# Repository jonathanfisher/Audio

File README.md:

# Overview
Now that I work for an audio company, I should really learn more about the various technology that goes into making things sound great. I've decided to spend some time designing my own audio setup (outside of making my own speaker). This project is intended as a learning exercise, not as a product to sell. As such, the commits here may take interesting twists and turns.

# Repository
This repository contains the design files for the PCBs I intend to make. The idea is to eventually design the following stages:

1. [USB](#USB)
2. [DAC](#DAC)
3. [Amplifier](#Amplifier)

I intend to design these as discrete boards that can be chained together. This modular design should allow me to more easily iterate in things I care about. I imagine that I will make mistakes along the way, and will have to re-spin boards.

## USB
This stage is intended to be the interface between a digital audio source (e.g. computer) and the rest of the audio system. USB seemed to be a reasonable medium to use for this.

## DAC
This stage is responsible for receiving a stream of digital signals and converting it to an analog output that can be converted to sound by a speaker.

## Amplifier
This stage is responsible for taking the output of the DAC and amplifying it so that the speaker(s) output the desired level of sound.

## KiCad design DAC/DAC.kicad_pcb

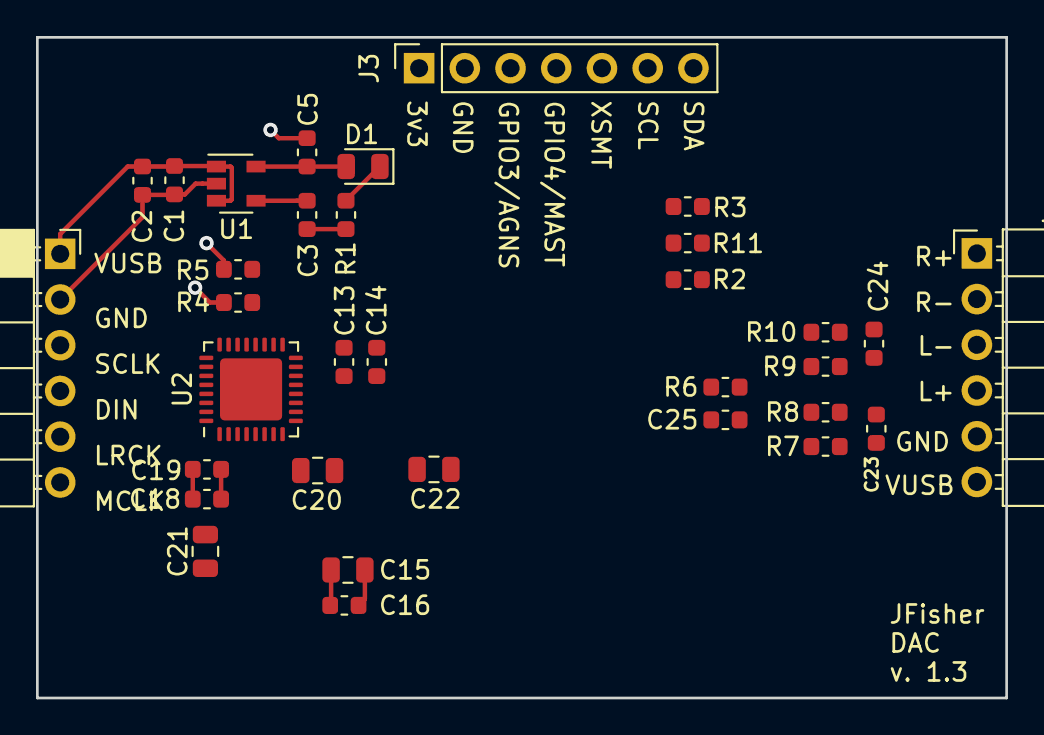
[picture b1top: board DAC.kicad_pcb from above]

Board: 4 copper layers, 53.8 x 36.7 mm, 33 parts (0 on the bottom side), 30 nets.

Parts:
C1, C13, C18: 10uF; C_0603_1608Metric
C2, C14, C16, C19: 0.1uF; C_0603_1608Metric
C3: 0.01uF; C_0603_1608Metric
C5: 1uF; C_0603_1608Metric
C15, C20, C22: 2.2uF; C_0805_2012Metric
C21: 0.1uF; C_0805_2012Metric
C23, C24: 1000pF; C_0603_1608Metric
C25: 1.0uF; C_0603_1608Metric
D1: LED_3v3; LED_0805_2012Metric
J1: Conn_01x06; PinSocket_1x06_P2.54mm_Horizontal
J2: Conn_01x06; PinHeader_1x06_P2.54mm_Horizontal
J3: Conn_01x07_Male; PinSocket_1x07_P2.54mm_Vertical
R1: 360; R_0603_1608Metric
R2, R11: 4.7k; R_0603_1608Metric
R3, R4, R5: 4.99k; R_0603_1608Metric
R6: 0; R_0603_1608Metric
R7, R8, R9, R10: 499; R_0603_1608Metric
U1: TPS73633DBV; SOT-23-5
U2: PCM5242RHB; Texas_S-PVQFN-N32_EP3.45x3.45mm

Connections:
+3V3: C5.1, C13.1, C14.1, C15.1, C16.1, C18.1, C19.1, D1.2, J3.1, R2.1, R3.2, R4.2, R11.1, U1.5, U2.4, U2.5, U2.14
DACL+: C23.1, J2.4, R7.1
DACL-: C23.2, J2.3, R8.1
DACR+: C24.2, J2.1, R10.1
DACR-: C24.1, J2.2, R9.1
GND: C1.2, C2.2, C3.2, C5.2, C13.2, C14.2, C15.2, C16.2, C18.2, C19.2, C21.2, C22.2, C25.2, J1.2, J2.5, J3.2, R1.2, R5.2, R6.1, U1.2, U2.3, U2.7, U2.15, U2.22, U2.32
GPIO3_AGNS: J3.3, U2.21
GPIO4_MAST: J3.4, U2.20
GPIO5_ATT0: J1.6, U2.19
GPIO6_FLT: U2.25, U2.26
I2S_DIN: J1.4, U2.28
I2S_LRCK: J1.5, U2.31
I2S_SCLK: J1.3, U2.27
MODE1: R5.1, U2.23
MODE2: R4.1, U2.24
unnamed: C3.1, U1.4
unnamed: C20.1, U2.6
unnamed: C20.2, U2.8
unnamed: C21.1, U2.2
unnamed: C22.1, U2.9
unnamed: C25.1, R6.2, U2.16
unnamed: D1.1, R1.1
OUTL_N: R8.2, U2.11
OUTL_P: R7.2, U2.10
OUTR_N: R9.2, U2.12
OUTR_P: R10.2, U2.13
SCL_MC_ATT1: J3.6, R2.2, U2.18
SDA_MOSI_ATT2: J3.7, R11.2, U2.17
VUSB: C1.1, C2.1, J1.1, J2.6, U1.1, U1.3
XSMT: J3.5, R3.1, U2.1

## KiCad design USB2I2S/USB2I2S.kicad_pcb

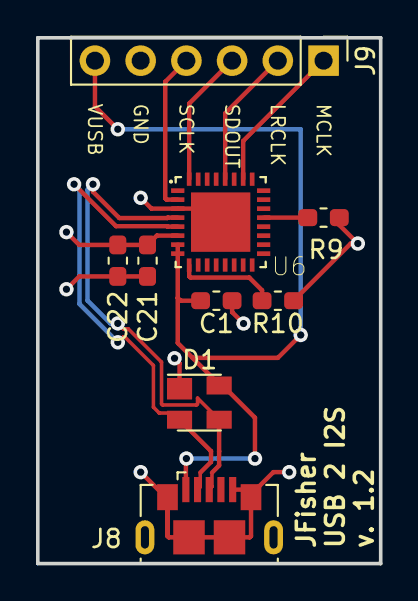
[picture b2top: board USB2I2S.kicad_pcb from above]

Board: 4 copper layers, 19.1 x 29.2 mm, 9 parts (0 on the bottom side), 11 nets.

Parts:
C1, C21: 1uF; C_0603_1608Metric_Pad1.05x0.95mm_HandSolder
C22: 0.1uF; C_0603_1608Metric_Pad1.05x0.95mm_HandSolder
D1: SP0503BAHT; SOT-143
J8: USB_B_Micro; USB_Micro-B_GCT_USB3076-30-A
J9: Conn_01x06_Male; PinHeader_1x06_P2.54mm_Vertical
R9, R10: 4.7K; R_0603_1608Metric_Pad1.05x0.95mm_HandSolder
U6: CP2615-A01-GM; QFN50P500X500X90-33N

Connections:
GND: C1.2, C21.2, C22.2, D1.1, J8.5, J8.6, J9.5, U6.3, U6.33
I2S_LRCLK: J9.2, U6.28
I2S_MCLK: J9.1, U6.26
I2S_SCLK: J9.4, U6.2
I2S_SDOUT: J9.3, U6.32
unnamed: R9.2, U6.21
unnamed: R10.2, U6.9
USB_DN: D1.2, J8.2, U6.5
USB_DP: D1.3, J8.3, U6.4
VBUS_IN: C1.1, D1.4, J8.1, J9.6, U6.7, U6.8
VCC: C21.1, C22.1, R9.1, R10.1, U6.6

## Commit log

2019-02-13 Initial commit with basic files for Audio DAC
2019-02-15 Add library containing CP2615 part
2019-02-15 Add schematic for the USB -> I2S stage
2019-02-15 Bring in project with multi-page design
2019-02-19 Add components for creating 3v3 for the DAC power rails
2019-03-07 Schematic and board file for USB2I2S dongle
2019-03-07 Update gitignore to account for more temp files
2019-03-11 Start designing the DAC stage
2019-03-17 Remove old and unused scratch files
2019-03-18 Create symbol for the PCM5242 DAC from TI
2019-03-18 Add sheet for the actual DAC part
2019-03-18 Add sheet for power conversion (USB -> 3v3 for now)
2019-03-18 Add Sheets for the I/O for this board. Still WIP on output
2019-03-18 Bring changes together in outmost sheet. This should just pull together the various subsheets
2019-03-18 Remove unused I/V stage on output of DAC
2019-03-19 Add new sheet for amplifier (post i-v stage)
    I'm not sure if I'll stick with this here; my thinking is that it makes
    sense to keep the post I-V stage amplifier on the same PCB as the DAC to
    minimize noise on the amplifier input. I imagine that PCB interconnects
    would cause a fairly significant amount of noise, so I'd like to avoid
    that.
2019-03-19 Remove absolute paths
2019-03-21 Adding support for headphone amp (WIP)
2019-03-22 Started layout of the DAC board
2019-03-25 Update USB2I2S board to fix routing issue
    - Fixed issue where VCC was connected to VUSB
    - Converted PCB to 4-layer board with Vcc and GND planes
    - Removed headers for pins that I'm not expecting to use
    - Re-layed out the PCB.
2019-03-25 Update KiCad and minor adjustments (cosmetic)
    Rotated the decoupling caps on Vcc to ensure that the blind vias were
    away from the differential USB signal traces.
2019-03-26 Remove extraneous directory (DAC/DAC/ -> DAC/)
2019-03-26 Removed file left over from earlier days that is no longer used
2019-03-26 Added first pass at routing the DAC PCB
2019-03-26 Update routing of DAC board
    - Route differential outputs with matching lengths
    - Add silkscreen labels for inputs and outputs
2019-03-26 Updated routing information & silk screens
    - Update pin names of differential outputs of PCM5242
    - Better alignment of silkscreen component labels
2019-03-27 Convert blind vias to through vias
2019-04-01 Convert blind vias to through and minor silkscreen changes
    This is the version released to be made
2019-04-01 Convert blind vias to through and update DAC layout
    This will constitute the first spin of the DAC board.
2019-04-13 Fixed the VUSB <-> REGIN error causing board not to create Vcc.
2019-09-28 Update DAC to expose config pins and to use larger components
2019-09-28 Ignore some more cache & backup files
2019-09-28 Update PCB placement
2019-09-29 Add headers for MCLK/SCLK signal to allow for clock workaround
    This helps to address the issue called out in the datasheet: https://e2e.ti.com/support/audio/f/6/p/804836/2980033#2980033, allowing the DAC to receive the MCLK input and create a usable SCLK input f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
2019-09-29 Work around DAC incompatibility with I2S clock (#4)
    * Update DAC to expose config pins and to use larger components
    * Ignore some more cache & backup files
    * Update PCB placement
    * Add headers for MCLK/SCLK signal to allow for clock workaround
    This helps to address the issue called out in the datasheet: https://e2e.ti.com/support/audio/f/6/p/804836/2980033#2980033, allowing the DAC to receive the MCLK input and create a usable SCLK input f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
2019-09-29 Update README with some renderings of PCBs
2019-11-26 Fix GPIO labeling on DAC silk screen (Issue #5)
    The GPIO labels were incorrectly placed and thus wrong.
2020-02-06 Generate base project for NUCLEO-STM32F7
    This project will hold the code responsible for the USB to I2S conversion. Currently it contains just the stock generated code for the USB audio device.
2020-02-06 :sparkles: Enable I2C interface & call pcm5242 init
2020-02-06 :sparkles: Add reset function and include pcm5242 directory in build
2020-02-06 Update heap space to 16kbytes
    This sets aside enough space to store 80 packets of audio data @ 48khz @ 16 bits per sample @ 2 channels
2020-02-06 :art: Document and reformat code
2020-02-06 Ignore the stm32f7 build files
2020-02-06 WIP: Start adding interface for PCM5242
    This code compiles but has not been run on hardware at all.
2020-02-08 :fire: Remove ethernet and move I2C port to more accessible pins
    Note that this commit also mucks with the line endings, which is annoying.
2020-02-13 :art: Add function call to get pcm5242 status
    This is mostly just sugar, adding an enum and boolean to make it easier to read the chip state
2020-02-13 :art: Undefine a macro after it's been used
    The macro for defining registers should not be used anywhere else in the file. This helps to enforce that.
2020-02-13 :ambulance: Fix issue where undef-ing nested macro causes compile issues
    Because a #define relies on a macro, undefining the macro causes compile-time issues when the substitutions are made.
2020-02-13 :art: Add separating comment for static functions
2020-02-13 :sparkles: Add helper function for calculating sine wave samples
    This is not used yet
2020-02-13 :art: Change the formatting of a function implementation
2020-02-14 :construction: Add some math for calculating output sine wave
2020-02-16 :sparkles: Enable I2S pins and transmit sine wave
2020-02-17 :sparkles: Plays a 1khz sine wave @ 44100 sample rate
    Switching from cos() to cosf() was the large change that seemed to ensure that the wave could be calculated fast enough
2020-03-10 Add python scripts for analyzing audio data
2020-03-11 Plot windowed data
2020-03-11 Plot audio data from the saleae and ap machine
2020-03-12 Add analysis python code for windowing
